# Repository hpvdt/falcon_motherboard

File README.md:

# Motherboard

Firmware and hardware designs for the Falcon motherboard.

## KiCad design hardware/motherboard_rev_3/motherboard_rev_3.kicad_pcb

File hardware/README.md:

# Motherboard Hardware

These are the collected files for all the custom circuit boards for the Falcon aircraft project. All circuits were designed in KiCad.

## Revision 0.0

An initial design by a former team member, never actually produced. Merely kept for reference.

## Revision 1.0

First revision made by Aryan Ghosh, based on 0.0. Although produced it had some design issues and wasn't developed much from a firmware perspective.

## Revision 2.0

A revision of the previous revision to address some issues as well as implement novel features. Led by Ethan.

## Revision 3.0

A heavy revision of the previous motherboard, spurred by changes in the architecture of the aircraft's embedded system, namely the transition to using a CAN bus for most inter board communication. Other notable changes:

- Removal of the RPi header intended for ANT biometric readings, not used anymore
- On boarding of the orientation sensor (BNO055)
- Removal of the LIDAR header
- Removal of the obsoleted OneWire header and hardware
- Moving to a new sensor for temperature and humidity
- Embedding of a power sensor to monitor battery use

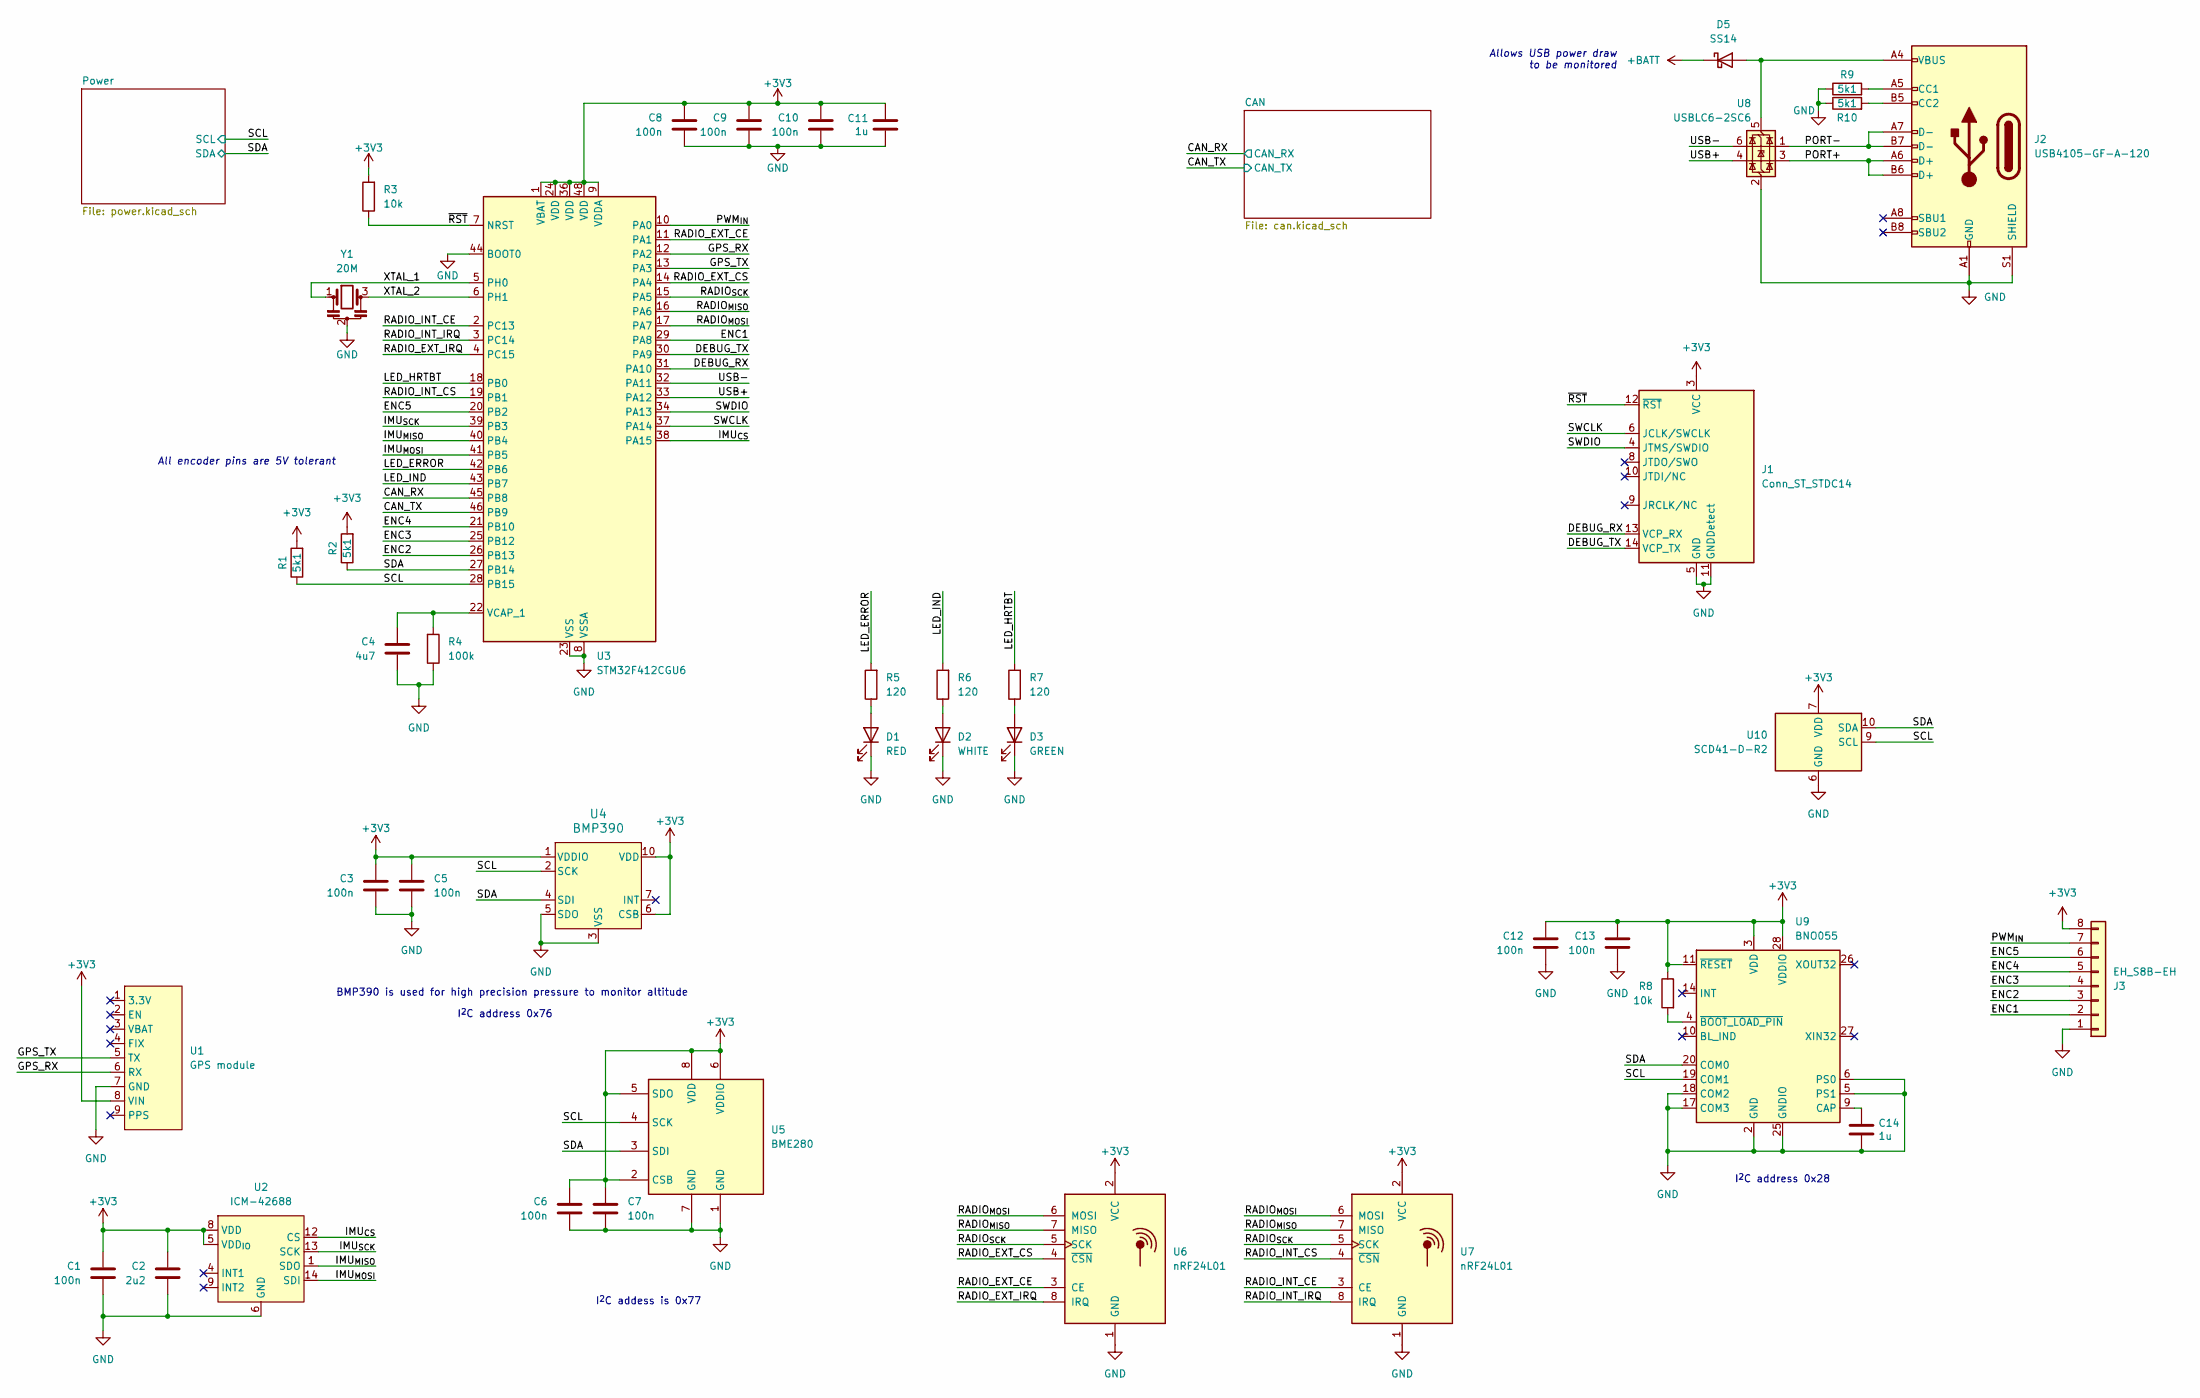
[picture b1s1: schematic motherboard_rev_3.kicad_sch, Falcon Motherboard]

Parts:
C1, C3, C5, C6, C7, C8, C9, C10, C12, C13: 100n; C_0402_1005Metric; LCSC C301928
C2: 2u2; C_0402_1005Metric; LCSC C12530
C4: 4u7; C_0603_1608Metric; LCSC C1705
C11, C14: 1u; C_0402_1005Metric; LCSC C52923
D1: RED; LED_0805_2012Metric; LCSC C84256
D2: WHITE; LED_0805_2012Metric; LCSC C34499
D3: GREEN; LED_0805_2012Metric; LCSC C2293
D5: SS14; D_SOD-123F; LCSC C2909920
J1: Conn_ST_STDC14; PinHeader_2x07_P1.27mm_Vertical_SMD; LCSC C2881912
J2: USB4105-GF-A-120; USB_C_Receptacle_GCT_USB4105-xx-A_16P_TopMnt_Horizontal; LCSC C5184243
J3: EH_S8B-EH; JST_EH_S8B-EH_1x08_P2.50mm_Horizontal; LCSC C265106
R1, R2, R9, R10: 5k1; R_0402_1005Metric; LCSC C25905
R3, R8: 10k; R_0402_1005Metric; LCSC C723353
R4: 100k; R_0402_1005Metric; LCSC C25530
R5, R6, R7: 120; R_0402_1005Metric; LCSC C25079
U1: GPS module; PinSocket_1x09_P2.54mm_Vertical
U2: ICM-42688; LGA-14_3x2.5mm_P0.5mm_LayoutBorder3x4y; LCSC C1850418
U3: STM32F412CGU6; QFN-48-1EP_7x7mm_P0.5mm_EP5.6x5.6mm; LCSC C2055817
U4: BMP390; LGA10_BMP390_BOS; LCSC C5124834
U5: BME280; Bosch_LGA-8_2.5x2.5mm_P0.65mm_ClockwisePinNumbering; LCSC C92489
U6, U7: nRF24L01; nRF24L01_Breakout
U8: USBLC6-2SC6; SOT-23-6; LCSC C7519
U9: BNO055; LGA-28_5.2x3.8mm_P0.5mm; LCSC C93216
U10: SCD41-D-R2; Sensirion_SCD4x-1EP_10.1x10.1mm_P1.25mm_EP4.8x4.8mm
Y1: 20M; Resonator_SMD_Murata_CSTxExxV-3Pin_3.0x1.1mm; LCSC C2650766

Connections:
+3V3: C1.1, C2.1, C3.1, C5.1, C6.1, C7.1, C8.1, C9.1, C10.1, C11.2, C12.1, C13.1, J1.3 (VCC), J3.8, R1.2, R2.2, R3.2, R8.1, U1.8 (VIN), U2.5 (VDD_{IO}), U2.8 (VDD), U3.1 (VBAT), U3.9 (VDDA), U3.24 (VDD), U3.36 (VDD), U3.48 (VDD), U4.1 (VDDIO), U4.6 (CSB), U4.10 (VDD), U5.2 (CSB), U5.5 (SDO), U5.6 (VDDIO), U5.8 (VDD), U6.2 (VCC), U7.2 (VCC), U9.3 (VDD), U9.11 (~RESET), U9.28 (VDDIO), U10.7 (VDD), U10.19 (VDD); also elsewhere on the board
+BATT: D5.1 (K); also elsewhere on the board
/CAN_RX: U3.45 (PB8); also elsewhere on the board
/CAN_TX: U3.46 (PB9); also elsewhere on the board
/DEBUG_RX: J1.13 (VCP_RX), U3.31 (PA10)
/DEBUG_TX: J1.14 (VCP_TX), U3.30 (PA9)
/ENC1: J3.2, U3.29 (PA8)
/ENC2: J3.3, U3.26 (PB13)
/ENC3: J3.4, U3.25 (PB12)
/ENC4: J3.5, U3.21 (PB10)
/ENC5: J3.6, U3.20 (PB2)
/GPS_RX: U1.6 (RX), U3.12 (PA2)
/GPS_TX: U1.5 (TX), U3.13 (PA3)
/IMU_{CS}: U2.12 (CS), U3.38 (PA15)
/IMU_{MISO}: U2.1 (SDO), U3.40 (PB4)
/IMU_{MOSI}: U2.14 (SDI), U3.41 (PB5)
/IMU_{SCK}: U2.13 (SCK), U3.39 (PB3)
/LED_ERROR: R5.2, U3.42 (PB6)
/LED_HRTBT: R7.2, U3.18 (PB0)
/LED_IND: R6.2, U3.43 (PB7)
/PORT+: J2.A6 (D+), J2.B6 (D+), U8.3 (I/O2)
/PORT-: J2.A7 (D-), J2.B7 (D-), U8.1 (I/O1)
/PWM_{IN}: J3.7, U3.10 (PA0)
/RADIO_EXT_CE: U3.11 (PA1), U6.3 (CE)
/RADIO_EXT_CS: U3.14 (PA4), U6.4 (~CSN)
/RADIO_EXT_IRQ: U3.4 (PC15), U6.8 (IRQ)
/RADIO_INT_CE: U3.2 (PC13), U7.3 (CE)
/RADIO_INT_CS: U3.19 (PB1), U7.4 (~CSN)
/RADIO_INT_IRQ: U3.3 (PC14), U7.8 (IRQ)
/RADIO_{MISO}: U3.16 (PA6), U6.7 (MISO), U7.7 (MISO)
/RADIO_{MOSI}: U3.17 (PA7), U6.6 (MOSI), U7.6 (MOSI)
/RADIO_{SCK}: U3.15 (PA5), U6.5 (SCK), U7.5 (SCK)
/SCL: R1.1, U3.28 (PB15), U4.2 (SCK), U5.4 (SCK), U9.19 (COM1), U10.9 (SCL); also elsewhere on the board
/SDA: R2.1, U3.27 (PB14), U4.4 (SDI), U5.3 (SDI), U9.20 (COM0), U10.10 (SDA); also elsewhere on the board
/SWCLK: J1.6 (JCLK/SWCLK), U3.37 (PA14)
/SWDIO: J1.4 (JTMS/SWDIO), U3.34 (PA13)
/USB+: U3.33 (PA12), U8.4 (I/O2)
/USB-: U3.32 (PA11), U8.6 (I/O1)
/XTAL_1: U3.5 (PH0), Y1.1
/XTAL_2: U3.6 (PH1), Y1.3
/~RST: J1.12 (~RST), R3.1, U3.7 (NRST)
GND: C1.2, C2.2, C3.2, C4.2, C5.2, C6.2, C7.2, C8.2, C9.2, C10.2, C11.1, C12.2, C13.2, C14.1, D1.1 (K), D2.1 (K), D3.1 (K), J1.5 (GND), J1.7 (GND), J1.11 (GNDDetect), J2.A1 (GND), J2.A12 (GND), J2.B1 (GND), J2.B12 (GND), J2.S1 (SHIELD), J3.1, R4.1, R9.1, R10.1, U1.7 (GND), U2.2 (RESV), U2.3 (RESV), U2.6 (GND), U2.7 (GND), U2.10 (RESV), U2.11 (RESV), U3.8 (VSSA), U3.23 (VSS), U3.35 (VSS), U3.44 (BOOT0), U3.47 (VSS), U3.49 (VSS), U4.3 (VSS), U4.5 (SDO), U4.8 (VSS), U4.9 (VSS), U5.1 (GND), U5.7 (GND), U6.1 (GND), U7.1 (GND), U8.2 (GND), U9.2 (GND), U9.5 (PS1), U9.6 (PS0), U9.17 (COM3), U9.18 (COM2), U9.25 (GNDIO), U10.6 (GND), U10.20 (GND), U10.21 (GND), Y1.2; also elsewhere on the board
unnamed: D1.2 (A), R5.1
unnamed: D2.2 (A), R6.1
unnamed: D3.2 (A), R7.1
unnamed: D5.2 (A), J2.A4 (VBUS), J2.A9 (VBUS), J2.B4 (VBUS), J2.B9 (VBUS), U8.5 (VBUS)
unnamed: J2.A5 (CC1), R9.2
unnamed: J2.B5 (CC2), R10.2
unnamed: C4.1, R4.2, U3.22 (VCAP_1)
unnamed: C14.2, U9.9 (CAP)
unnamed: R8.2, U9.4 (~BOOT_LOAD_PIN)

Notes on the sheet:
All encoder pins are 5V tolerant
BMP390 is used for high precision pressure to monitor altitude
Allows USB power draw to be monitored
I^{2}C addess is 0x77
I^{2}C address 0x28
I^{2}C address 0x76

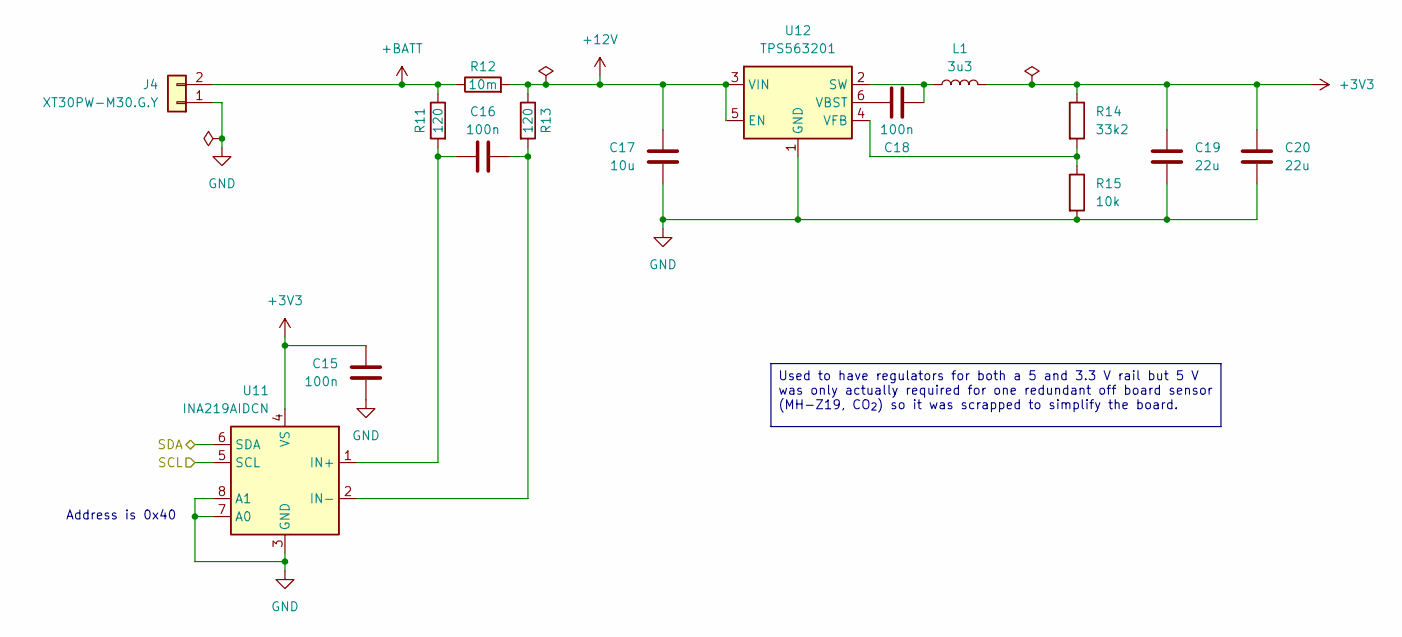
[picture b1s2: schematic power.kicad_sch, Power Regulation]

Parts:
C15, C16, C18: 100n; C_0402_1005Metric; LCSC C301928
C17: 10u; C_0603_1608Metric; LCSC C5360828
C19, C20: 22u; C_0603_1608Metric; LCSC C86295
J4: XT30PW-M30.G.Y; AMASS_XT30PW-M_1x02_P2.50mm_Horizontal; LCSC C431092
L1: 3u3; L_Changjiang_FNR6045S; LCSC C168063
R11, R13: 120; R_0402_1005Metric; LCSC C25079
R12: 10m; R_0805_2012Metric; LCSC C601083
R14: 33k2; R_0402_1005Metric; LCSC C122548
R15: 10k; R_0402_1005Metric; LCSC C723353
U11: INA219AIDCN; SOT-23-8; LCSC C87469
U12: TPS563201; SOT-23-6; LCSC C116592

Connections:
+3V3: C15.1, C19.1, C20.1, L1.2, R14.1, U11.4 (VS); also elsewhere on the board
+12V: C17.1, R12.2, R13.1, U12.3 (VIN), U12.5 (EN); also elsewhere on the board
+BATT: J4.2, R11.1, R12.1; also elsewhere on the board
/SCL: U11.5 (SCL); also elsewhere on the board
/SDA: U11.6 (SDA); also elsewhere on the board
GND: C15.2, C17.2, C19.2, C20.2, J4.1, R15.2, U11.3 (GND), U11.7 (A0), U11.8 (A1), U12.1 (GND); also elsewhere on the board
unnamed: C16.2, R11.2, U11.1 (IN+)
unnamed: C16.1, R13.2, U11.2 (IN-)
unnamed: C18.2, L1.1, U12.2 (SW)
unnamed: C18.1, U12.6 (VBST)
unnamed: R14.2, R15.1, U12.4 (VFB)

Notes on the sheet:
Address is 0x40
Used to have regulators for both a 5 and 3.3 V rail but 5 V was only actually required for one redundant off board sensor (MH-Z19, CO_{2}) so it was scrapped to simplify the board.

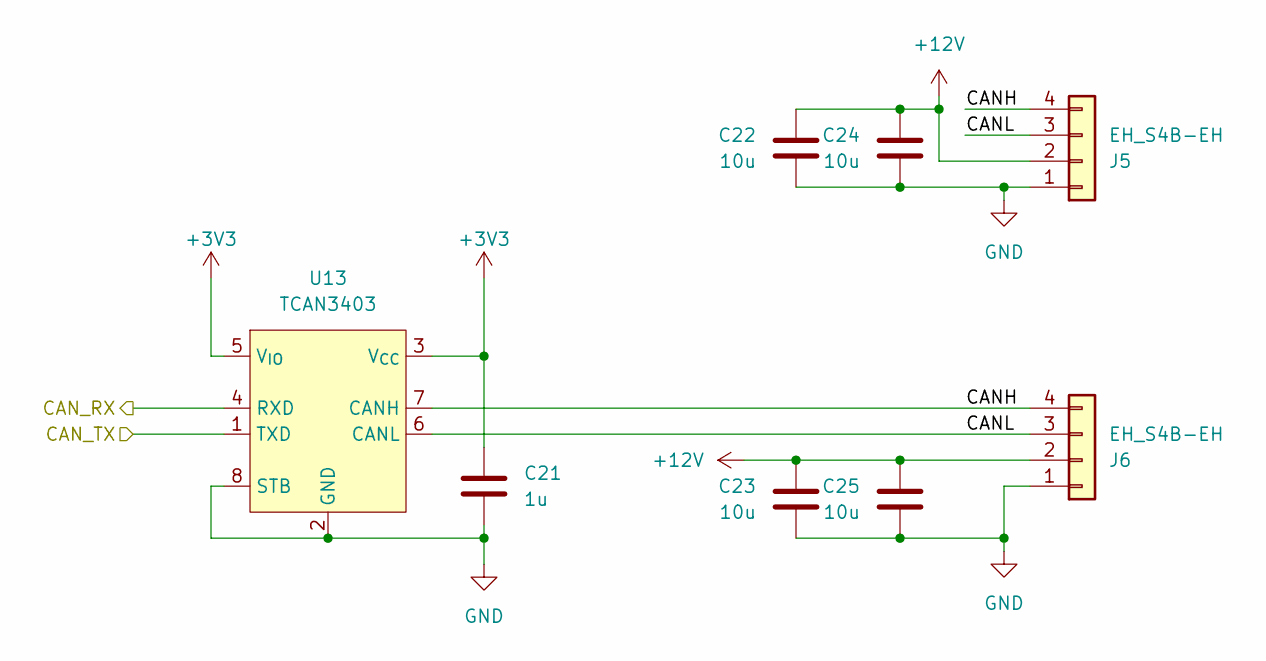
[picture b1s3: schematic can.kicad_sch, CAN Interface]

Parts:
C21: 1u; C_0402_1005Metric; LCSC C52923
C22, C23, C24, C25: 10u; C_0603_1608Metric; LCSC C5360828
J5, J6: EH_S4B-EH; JST_EH_S4B-EH_1x04_P2.50mm_Horizontal; LCSC C265068
U13: TCAN3403; TSOT-23-8; LCSC C35926232

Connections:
+3V3: C21.1, U13.3 (V_{CC}), U13.5 (V_{IO}); also elsewhere on the board
+12V: C22.1, C23.1, C24.1, C25.1, J5.2, J6.2; also elsewhere on the board
/CAN/CANH: J5.4, J6.4, U13.7 (CANH)
/CAN/CANL: J5.3, J6.3, U13.6 (CANL)
/CAN_RX: U13.4 (RXD); also elsewhere on the board
/CAN_TX: U13.1 (TXD); also elsewhere on the board
GND: C21.2, C22.2, C23.2, C24.2, C25.2, J5.1, J6.1, U13.2 (GND), U13.8 (STB); also elsewhere on the board

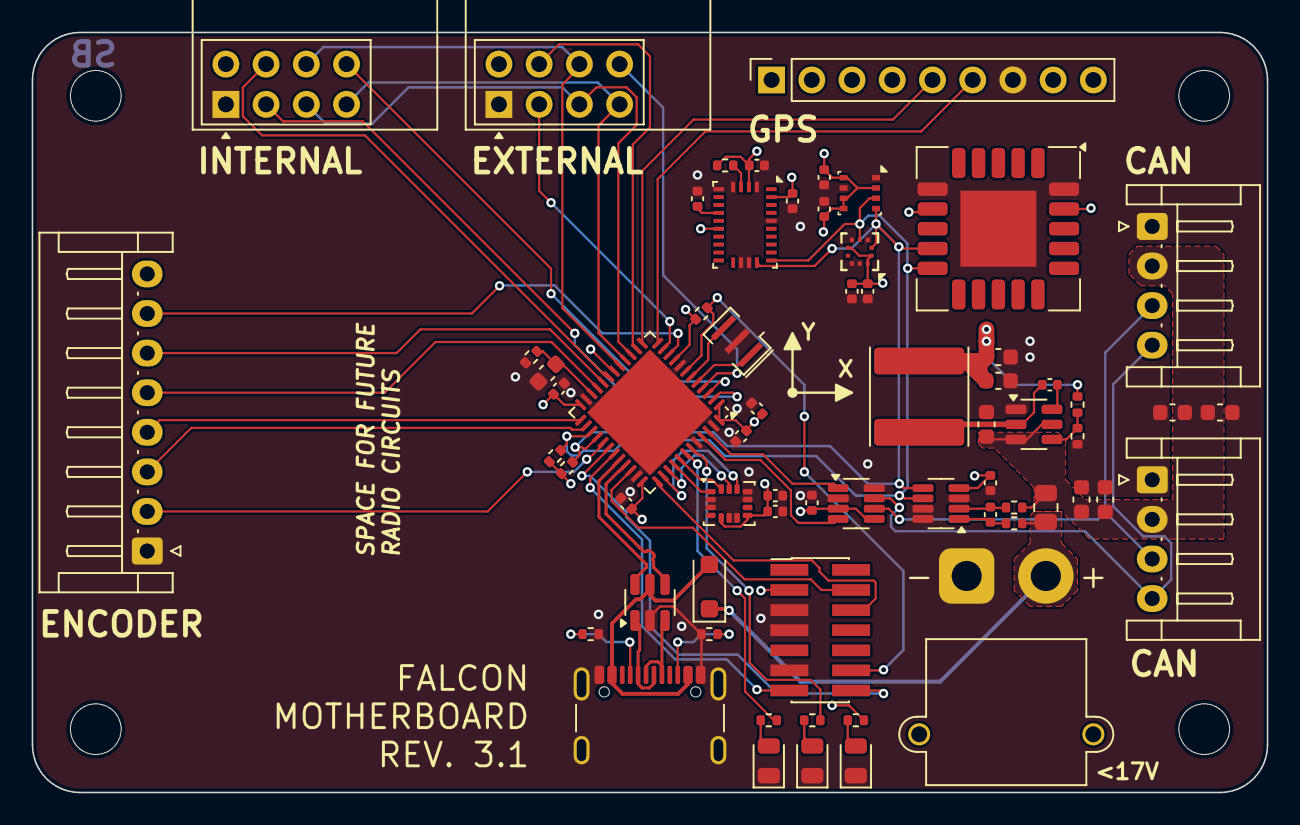
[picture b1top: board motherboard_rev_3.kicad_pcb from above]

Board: 4 copper layers, 78.0 x 48.0 mm, 65 parts (0 on the bottom side), 59 nets.

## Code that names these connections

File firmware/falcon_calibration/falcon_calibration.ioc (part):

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Mcu.Name=STM32F412C(E-G)Ux
Mcu.Package=UFQFPN48
Mcu.UserName=STM32F412CGUx
PA0.GPIOParameters=GPIO_PuPd,GPIO_Label
PA0.GPIO_Label=PWM_IN
PA0.GPIO_PuPd=GPIO_PULLDOWN
PA0.Signal=S_TIM2_CH1_ETR
PA1.GPIOParameters=GPIO_Label
PA1.GPIO_Label=RADIO_EXT_CE
PA1.Signal=GPIO_Output
PA10.GPIOParameters=GPIO_Label
PA10.GPIO_Label=DEBUG_RX
PA10.Mode=Asynchronous
PA10.Signal=USART1_RX
PA11.Mode=Device_Only
PA11.Signal=USB_OTG_FS_DM
PA12.Mode=Device_Only
PA12.Signal=USB_OTG_FS_DP
PA13.Mode=Serial_Wire
PA13.Signal=SYS_JTMS-SWDIO
PA14.Mode=Serial_Wire
PA14.Signal=SYS_JTCK-SWCLK
PA15.GPIOParameters=GPIO_Label
PA15.GPIO_Label=IMU_CS
PA15.Mode=NSS_Signal_Hard_Output
PA15.Signal=SPI3_NSS
PA2.GPIOParameters=GPIO_Label
PA2.GPIO_Label=GPS_RX
PA2.Mode=Asynchronous
PA2.Signal=USART2_TX
PA3.GPIOParameters=GPIO_Label
PA3.GPIO_Label=GPS_TX
PA3.Mode=Asynchronous
PA3.Signal=USART2_RX
PA4.GPIOParameters=GPIO_Label
PA4.GPIO_Label=RADIO_EXT_CS
PA4.Signal=GPIO_Output
PA5.GPIOParameters=GPIO_Label
PA5.GPIO_Label=RADIO_SCK
PA5.Mode=Full_Duplex_Master
PA5.Signal=SPI1_SCK
PA6.GPIOParameters=GPIO_Label
PA6.GPIO_Label=RADIO_MISO
PA6.Mode=Full_Duplex_Master
PA6.Signal=SPI1_MISO
PA7.GPIOParameters=GPIO_Label
PA7.GPIO_Label=RADIO_MOSI
PA7.Mode=Full_Duplex_Master
PA7.Signal=SPI1_MOSI
PA8.GPIOParameters=GPIO_PuPd,GPIO_Label
PA8.GPIO_Label=ENC_1
PA8.GPIO_PuPd=GPIO_PULLDOWN
PA8.Signal=S_TIM1_CH1
PA9.GPIOParameters=GPIO_Label
PA9.GPIO_Label=DEBUG_TX
PA9.Mode=Asynchronous
PA9.Signal=USART1_TX
PB0.GPIOParameters=GPIO_Label
PB0.GPIO_Label=LED_HEARTBEAT
PB0.Signal=S_TIM3_CH3
PB1.GPIOParameters=GPIO_Label
PB1.GPIO_Label=RADIO_INT_CS
PB1.Signal=GPIO_Output
PB10.GPIOParameters=GPIO_PuPd,GPIO_Label
PB10.GPIO_Label=ENC_4
PB10.GPIO_PuPd=GPIO_PULLDOWN
PB10.Signal=GPIO_Input
PB12.GPIOParameters=GPIO_PuPd,GPIO_Label
PB12.GPIO_Label=ENC_3
PB12.GPIO_PuPd=GPIO_PULLDOWN
PB12.Signal=GPIO_Input
PB13.GPIOParameters=GPIO_PuPd,GPIO_Label
PB13.GPIO_Label=ENC_2
PB13.GPIO_PuPd=GPIO_PULLDOWN
PB13.Signal=GPIO_Input
PB14.Mode=I2C
PB14.Signal=FMPI2C1_SDA
PB15.Mode=I2C
PB15.Signal=FMPI2C1_SCL
PB2.GPIOParameters=GPIO_PuPd,GPIO_Label
PB2.GPIO_Label=ENC_5
PB2.GPIO_PuPd=GPIO_PULLDOWN
PB2.Signal=GPIO_Input
PB3.GPIOParameters=GPIO_Label
PB3.GPIO_Label=IMU_SCK
PB3.Mode=Full_Duplex_Master
PB3.Signal=SPI3_SCK
PB4.GPIOParameters=GPIO_Label
PB4.GPIO_Label=IMU_MISO
PB4.Mode=Full_Duplex_Master
PB4.Signal=SPI3_MISO
PB5.GPIOParameters=GPIO_Label
PB5.GPIO_Label=IMU_MOSI
PB5.Mode=Full_Duplex_Master
PB5.Signal=SPI3_MOSI
PB6.GPIOParameters=GPIO_Label
PB6.GPIO_Label=LED_ERROR
PB6.Signal=S_TIM4_CH1
PB7.GPIOParameters=GPIO_Label
PB7.GPIO_Label=LED_INDICATOR
PB7.Signal=S_TIM4_CH2
PB8.Mode=CAN_Activate
PB8.Signal=CAN1_RX
PB9.Mode=CAN_Activate
PB9.Signal=CAN1_TX
PC13.GPIOParameters=GPIO_Label
PC13.GPIO_Label=RADIO_INT_CE
PC13.Signal=GPIO_Output
PC14-OSC32_IN.GPIOParameters=GPIO_PuPd,GPIO_Label
PC14-OSC32_IN.GPIO_Label=RADIO_INT_IRQ
PC14-OSC32_IN.GPIO_PuPd=GPIO_PULLUP
PC14-OSC32_IN.Signal=GPIO_Input
PC15-OSC32_OUT.GPIOParameters=GPIO_PuPd,GPIO_Label
PC15-OSC32_OUT.GPIO_Label=RADIO_EXT_IRQ
PC15-OSC32_OUT.GPIO_PuPd=GPIO_PULLUP
PC15-OSC32_OUT.Signal=GPIO_Input
PH0\ -\ OSC_IN.Mode=HSE-External-Oscillator
PH0\ -\ OSC_IN.Signal=RCC_OSC_IN
PH1\ -\ OSC_OUT.Mode=HSE-External-Oscillator
PH1\ -\ OSC_OUT.Signal=RCC_OSC_OUT
RCC.HSE_VALUE=20000000
RCC.SYSCLKFreq_VALUE=100000000
RCC.SYSCLKSource=RCC_SYSCLKSOURCE_PLLCLK
board=custom

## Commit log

2023-09-24 Initialized PlatformIO project
2024-01-26 Added basic test code for initial upload
2024-02-02 test
2024-02-02 Initial program for DPS310
2024-02-02 initial test code work
2024-02-02 note to look @ schematic
2024-02-02 work on initial test code
2024-02-10 Baseline USB functionality verified
    Issues found in hardware, USB D+ and D- signal are going to the wrong pins on the MCU of the rev. 1 board.
2024-02-23 code for test readings
2024-02-23 Cleaning up code
2024-02-23 Fixed pin allocations for IMU
2024-02-23 code to partially incorporate some LEDs
2024-02-23 code to partially incorporate LEDs
2024-03-01 importing previously written sensor code from other repos
2024-03-01 added source for example code
2024-03-01 added setup functions for BNO & DPS, fixed compile errors
2024-03-01 work on barometer & orientation test code
2024-03-01 added a note saying what to address next
2024-03-02 Barometer with USB
2024-03-08 adjusting setup fns to keep BNO object in main fn scope
2024-03-08 LIDAR test code work
2024-03-08 LIDAR I2C stuff to do in the future
2024-03-09 Working_Barometer
2024-03-09 fixed printf statement
2024-03-09 start of IMU wrapper functions
2024-03-10 Strain Gauge amps working
2024-03-10 inital radio test
2024-03-13 Radio
2024-03-22 sending iterating values to prop control board
2024-03-23 working CO2 + DHT test code
2024-03-23 IMU wrapper functions done
2024-03-23 Workig Lidar
2024-03-23 work on wrapper functions for dht
2024-03-27 setup + measurement wrapper functions
2024-03-27 made naming convention consistent, took unnecessary items out of scope
2024-03-27 normalized naming convention
2024-03-27 merged IMU, DHT, CO2 sensor libraries
2024-03-27 added print functions for IMU, DHT, and CO2 libraries
2024-03-27 Radio set to recieve acknowledgements
2024-03-27 Adafruit BNO055 library
2024-03-27 start of wrapper functions
2024-03-30 Fixed Arduino include
2024-03-30 Sending the correct payload
2024-04-03 Working GPS
2024-04-05 lidar wrapper functions fixed and code compiles
2024-04-05 Fixed BNO code
2024-04-05 Barometer changed to match previously working code
2024-04-10 checking if enough time has passed before reading values
2024-04-10 removing DHT & IMU reliance on global variables
2024-04-10 Working Lidar
2024-04-10 I2C bus declared in main
2024-04-12 Modified BNO libraries to allow setting I2C adress outside of constructor - ready to test
2024-04-13 Working code for all three sensors
2024-04-13 Gave IMU and DHT functions their required arguments
2024-04-29 Added correct libaries
2024-06-05 Wrapper functions for GPS
2024-06-05 Simplified for merge
2024-07-01 Communications to PC in raw format
2024-07-10 Reorganized radio code files
2024-07-10 Starting radio code
    Code is being reworked to keep most of radio work out of `main.cpp`.
    Reworked so references are used instead of pass-by-copy to make code
    easier to reuse safely.
    Also added constants for radios based on rev 3 schematic.
2024-07-10 Made `TinyGPS` a maintained library
    Moved `TinyGPS` library to be maintained by PlatformIO instead of a local
    copy in the event it is updated after 11+ years.
    Also tidied up the use of `#define`s replacing them with `const` expressions.
2024-07-10 Whitespacing to 4 spaces
2024-11-27 Adjusted whitespacing and some naming conventions
2024-11-27 Some more renaming and some scope reductions
2024-11-27 Changed from `double` to `float`
2024-11-27 Moved function descriptions to declaration
2024-11-27 Introduced some aircraft specific `struct`s
2024-11-27 Removed obsolete variables
2024-12-01 Added strain struct
2024-12-01 Drafted general message sending system
2024-12-04 Cleared `.vscode`
2024-12-04 Updated `.gitignore` to fully ignore `.vscode`
2024-12-04 Added comments for communications functions
2024-12-04 Removed conditional Arduino code from OneWire
2024-12-04 Added test function for OneWire
2024-12-04 Reduced OneWire bit period from 65 to 55us
2024-12-06 Fixed CO2 print
2024-12-06 Added remote control of OW testing modes
2024-12-06 Changed one wire testing to scan a range of nodes
2024-12-13 Including node address as part of checksum for tests
2024-12-13 Tuning OneWire
2024-12-15 Updated checksum for one wire protocol
2025-01-11 Adjusting strain struct to match built system
2025-01-11 LOAD TEST CODE
    Set up for the load test which was unattended by Savo.
    Performs a few self-tests of the strain gauges then prints their readings in human readable and CSV parsable text.
    Hope it works as intended!
2025-01-11 Fixed communication for pretty strain message
2025-01-11 SPAR LOAD TEST. Disabling irrelevant code.
2025-08-17 Reorganization of the folder and upload of the hardware designs
2025-08-20 Settled on pin out
2025-08-20 Started STM32CubeIDE project
2025-08-20 Completed schematic for rev 3.0 PCB
2025-08-20 Removed mention of EEPROM not instaled in the end
2025-08-20 Avoid KiCad recovery files
2025-08-23 Fixed up a symbol power pins
2025-08-23 Removed LDO and just regulate to 3.3V, also removed off board CO2
2025-08-23 Completed layout except for radio modules
2025-08-23 Added schematic for future integrated nRF24 modules
2025-08-23 Motherboard rev 3.1 as ordered
2025-09-07 Uploaded example of CDC on the motherboard
2025-09-07 Testing out USB on the main motherboard firmware
    Doesn't seem to work for some reason, perhaps a slight clash with other peripherals like TIM1 or USART1
2025-09-07 Deleted settings which shouldn't be monitored
2025-09-08 Configured motherboard for proper USB CDC
2025-09-13 Added LED code
2025-09-14 Added hardware UART `printf()`
2025-09-16 Achieved communication with wing modules
2025-10-26 Recorded correct node addresses for wing loads
2025-10-26 Started on calibration firmware
2025-10-26 Renamed project for general Falcon calibration
2025-10-26 Implemented calibration functions for load sensing
2025-10-26 Added calibration procedure to help command
2025-10-26 Fixed node numbers
2025-11-09 Completed driver for INA219 power sensor
2025-11-09 Added library for SCD41 CO2 sensor
2025-11-11 Prepared `README.md` for calibration firmware
2025-11-11 Minor touchup
2025-11-11 Added limits to parameters and warning for misinput
2025-11-11 Minor touch up
2025-11-11 Added command to restart periodic measurements
2025-11-11 Baseline BME280 driving
2025-11-12 Started atmospheric conditions wrapper
2025-11-12 Added support for BMP390 data
2025-11-13 Added section for wing load readings
2025-11-13 Added BMP390 specific interface config
2025-11-15 Touched up some scoping in atmospheric code
2025-11-15 Added in BNO055 and baseline orientation wrapper
2025-11-16 Ported communications code and adapted it for STM32Cube project
2026-01-14 Split initialization functions into separate files
2026-01-14 Imported a baseline nRF24 library
2026-01-14 Updated library to allow project to compile
2026-01-19 Working nRF24 RX
2026-03-29 Moved radio functions into separate file
2026-03-29 Updated flight data struct
